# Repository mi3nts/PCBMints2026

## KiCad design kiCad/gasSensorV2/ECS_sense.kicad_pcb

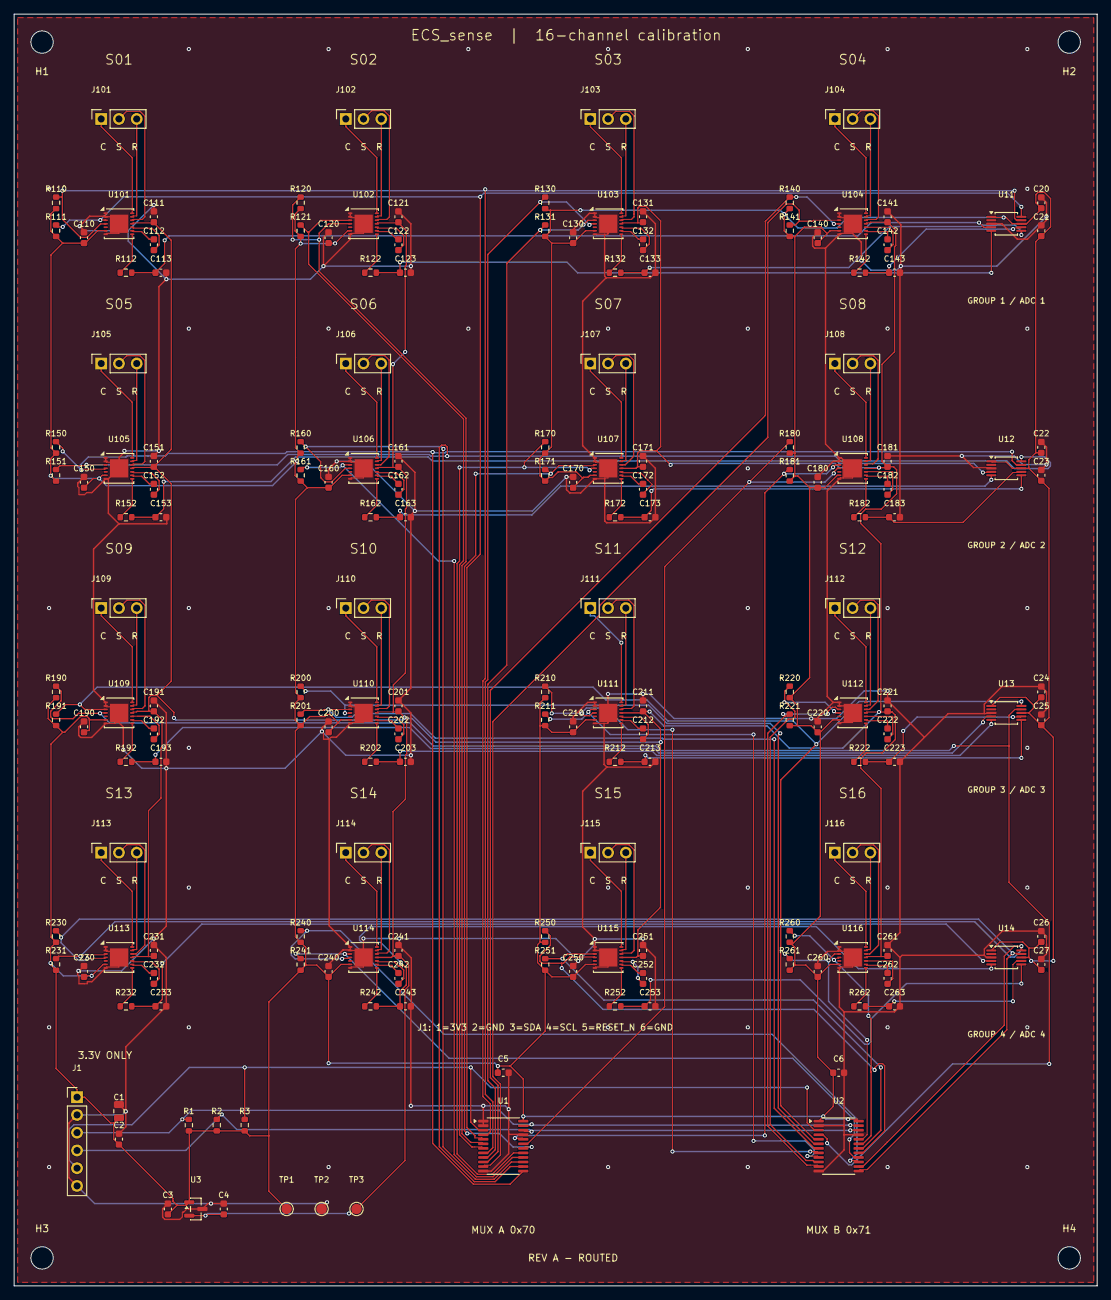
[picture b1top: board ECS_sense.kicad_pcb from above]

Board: 2 copper layers, 155.0 x 182.0 mm, 176 parts (0 on the bottom side), 150 nets.

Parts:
C1: 10uF / 10V; C_0805_2012Metric
C2, C5, C6, C20, C22, C24, C26, C110, C111, C113, C120, C121, C123, C130, C131, C133, C140, C141, C143, C150, C151, C153, C160, C161, C163, C170, C171, C173, C180, C181, C183, C190, C191, C193, C200, C201, C203, C210, C211, C213, C220, C221, C223, C230, C231, C233, C240, C241, C243, C250, C251, C253, C260, C261, C263: 100nF; C_0603_1608Metric
C3, C4, C21, C23, C25, C27: 1uF; C_0603_1608Metric
C112, C122, C132, C142, C152, C162, C172, C182, C192, C202, C212, C222, C232, C242, C252, C262: 10nF C0G; C_0603_1608Metric
H1, H2, H3, H4: MountingHole_3.2mm_M3
J1: MCU: 3V3 / GND / SDA / SCL / RESET / GND; PinHeader_1x06_P2.54mm_Vertical
J101, J102, J103, J104, J105, J106, J107, J108, J109, J110, J111, J112, J113, J114, J115, J116: ES1 port: C / S / R; PinSocket_1x03_P2.54mm_Vertical
R1, R2: 4.7k; R_0603_1608Metric
R3, R110, R111, R120, R121, R130, R131, R140, R141, R150, R151, R160, R161, R170, R171, R180, R181, R190, R191, R200, R201, R210, R211, R220, R221, R230, R231, R240, R241, R250, R251, R260, R261: 10k; R_0603_1608Metric
R112, R122, R132, R142, R152, R162, R172, R182, R192, R202, R212, R222, R232, R242, R252, R262: 100R; R_0603_1608Metric
TP1: 3V3; TestPoint_Pad_D1.5mm
TP2: GND; TestPoint_Pad_D1.5mm
TP3: 2V5; TestPoint_Pad_D1.5mm
U1, U2: TCA9548APWR; TSSOP-24_4.4x7.8mm_P0.65mm
U3: REF3025AIDBZR; SOT-23
U11, U12, U13, U14: ADS1115IDGS; TSSOP-10_3x3mm_P0.5mm
U101, U102, U103, U104, U105, U106, U107, U108, U109, U110, U111, U112, U113, U114, U115, U116: LMP91000SD; WSON-14-1EP_4.0x4.0mm_P0.5mm_EP2.6x2.6mm

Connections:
+3V3: C1.1, C2.1, C3.1, C5.1, C6.1, C20.1, C21.1, C22.1, C23.1, C24.1, C25.1, C26.1, C27.1, C110.1, C120.1, C130.1, C140.1, C150.1, C160.1, C170.1, C180.1, C190.1, C200.1, C210.1, C220.1, C230.1, C240.1, C250.1, C260.1, J1.1, R1.1, R2.1, R3.1, R110.1, R111.1, R120.1, R121.1, R130.1, R131.1, R140.1, R141.1, R150.1, R151.1, R160.1, R161.1, R170.1, R171.1, R180.1, R181.1, R190.1, R191.1, R200.1, R201.1, R210.1, R211.1, R220.1, R221.1, R230.1, R231.1, R240.1, R241.1, R250.1, R251.1, R260.1, R261.1, TP1.1 (1_1), U1.24 (VCC), U2.1 (A0), U2.24 (VCC), U3.1 (IN), U11.1 (ADDR), U11.8 (VDD), U12.1 (ADDR), U12.8 (VDD), U13.1 (ADDR), U13.8 (VDD), U14.1 (ADDR), U14.8 (VDD), U101.6 (VDD), U102.6 (VDD), U103.6 (VDD), U104.6 (VDD), U105.6 (VDD), U106.6 (VDD), U107.6 (VDD), U108.6 (VDD), U109.6 (VDD), U110.6 (VDD), U111.6 (VDD), U112.6 (VDD), U113.6 (VDD), U114.6 (VDD), U115.6 (VDD), U116.6 (VDD)
GND: C1.2, C2.2, C3.2, C4.2, C5.2, C6.2, C20.2, C21.2, C22.2, C23.2, C24.2, C25.2, C26.2, C27.2, C110.2, C111.2, C113.2, C120.2, C121.2, C123.2, C130.2, C131.2, C133.2, C140.2, C141.2, C143.2, C150.2, C151.2, C153.2, C160.2, C161.2, C163.2, C170.2, C171.2, C173.2, C180.2, C181.2, C183.2, C190.2, C191.2, C193.2, C200.2, C201.2, C203.2, C210.2, C211.2, C213.2, C220.2, C221.2, C223.2, C230.2, C231.2, C233.2, C240.2, C241.2, C243.2, C250.2, C251.2, C253.2, C260.2, C261.2, C263.2, J1.2, J1.6, TP2.1 (1_1), U1.1 (A0), U1.2 (A1), U1.12 (GND), U1.21 (A2), U2.2 (A1), U2.12 (GND), U2.21 (A2), U3.3 (GND), U11.3 (GND), U12.3 (GND), U13.3 (GND), U14.3 (GND), U101.1 (DGND), U101.2 (~MENB), U101.7 (AGND), U101.15 (DAP), U102.1 (DGND), U102.2 (~MENB), U102.7 (AGND), U102.15 (DAP), U103.1 (DGND), U103.2 (~MENB), U103.7 (AGND), U103.15 (DAP), U104.1 (DGND), U104.2 (~MENB), U104.7 (AGND), U104.15 (DAP), U105.1 (DGND), U105.2 (~MENB), U105.7 (AGND), U105.15 (DAP), U106.1 (DGND), U106.2 (~MENB), U106.7 (AGND), U106.15 (DAP), U107.1 (DGND), U107.2 (~MENB), U107.7 (AGND), U107.15 (DAP), U108.1 (DGND), U108.2 (~MENB), U108.7 (AGND), U108.15 (DAP), U109.1 (DGND), U109.2 (~MENB), U109.7 (AGND), U109.15 (DAP), U110.1 (DGND), U110.2 (~MENB), U110.7 (AGND), U110.15 (DAP), U111.1 (DGND), U111.2 (~MENB), U111.7 (AGND), U111.15 (DAP), U112.1 (DGND), U112.2 (~MENB), U112.7 (AGND), U112.15 (DAP), U113.1 (DGND), U113.2 (~MENB), U113.7 (AGND), U113.15 (DAP), U114.1 (DGND), U114.2 (~MENB), U114.7 (AGND), U114.15 (DAP), U115.1 (DGND), U115.2 (~MENB), U115.7 (AGND), U115.15 (DAP), U116.1 (DGND), U116.2 (~MENB), U116.7 (AGND), U116.15 (DAP)
MUX_RESET_N: J1.5, R3.2, U1.3 (~RESET), U2.3 (~RESET)
S01_ADC: C113.1, R112.2, U11.4 (AIN0)
S01_C1: C112.1, U101.10 (C1)
S01_C2: C112.2, U101.9 (C2)
S01_CE: J101.1, U101.14 (CE)
S01_RE: J101.3, U101.13 (RE)
S01_SCL: R111.2, U1.5 (SC0), U11.10 (SCL), U101.3 (SCL)
S01_SDA: R110.2, U1.4 (SD0), U11.9 (SDA), U101.4 (SDA)
S01_VOUT: R112.1, U101.8 (VOUT)
S01_WE: J101.2, U101.12 (WE)
S02_ADC: C123.1, R122.2, U11.5 (AIN1)
S02_C1: C122.1, U102.10 (C1)
S02_C2: C122.2, U102.9 (C2)
S02_CE: J102.1, U102.14 (CE)
S02_RE: J102.3, U102.13 (RE)
S02_SCL: R121.2, U1.7 (SC1), U102.3 (SCL)
S02_SDA: R120.2, U1.6 (SD1), U102.4 (SDA)
S02_VOUT: R122.1, U102.8 (VOUT)
S02_WE: J102.2, U102.12 (WE)
S03_ADC: C133.1, R132.2, U11.6 (AIN2)
S03_C1: C132.1, U103.10 (C1)
S03_C2: C132.2, U103.9 (C2)
S03_CE: J103.1, U103.14 (CE)
S03_RE: J103.3, U103.13 (RE)
S03_SCL: R131.2, U1.9 (SC2), U103.3 (SCL)
S03_SDA: R130.2, U1.8 (SD2), U103.4 (SDA)
S03_VOUT: R132.1, U103.8 (VOUT)
S03_WE: J103.2, U103.12 (WE)
S04_ADC: C143.1, R142.2, U11.7 (AIN3)
S04_C1: C142.1, U104.10 (C1)
S04_C2: C142.2, U104.9 (C2)
S04_CE: J104.1, U104.14 (CE)
S04_RE: J104.3, U104.13 (RE)
S04_SCL: R141.2, U1.11 (SC3), U104.3 (SCL)
S04_SDA: R140.2, U1.10 (SD3), U104.4 (SDA)
S04_VOUT: R142.1, U104.8 (VOUT)
S04_WE: J104.2, U104.12 (WE)
S05_ADC: C153.1, R152.2, U12.4 (AIN0)
S05_C1: C152.1, U105.10 (C1)
S05_C2: C152.2, U105.9 (C2)
S05_CE: J105.1, U105.14 (CE)
S05_RE: J105.3, U105.13 (RE)
S05_SCL: R151.2, U1.14 (SC4), U12.10 (SCL), U105.3 (SCL)
S05_SDA: R150.2, U1.13 (SD4), U12.9 (SDA), U105.4 (SDA)
S05_VOUT: R152.1, U105.8 (VOUT)
S05_WE: J105.2, U105.12 (WE)
S06_ADC: C163.1, R162.2, U12.5 (AIN1)
S06_C1: C162.1, U106.10 (C1)
S06_C2: C162.2, U106.9 (C2)
S06_CE: J106.1, U106.14 (CE)
S06_RE: J106.3, U106.13 (RE)
S06_SCL: R161.2, U1.16 (SC5), U106.3 (SCL)
S06_SDA: R160.2, U1.15 (SD5), U106.4 (SDA)
S06_VOUT: R162.1, U106.8 (VOUT)
S06_WE: J106.2, U106.12 (WE)
S07_ADC: C173.1, R172.2, U12.6 (AIN2)
S07_C1: C172.1, U107.10 (C1)
S07_C2: C172.2, U107.9 (C2)
S07_CE: J107.1, U107.14 (CE)
S07_RE: J107.3, U107.13 (RE)
S07_SCL: R171.2, U1.18 (SC6), U107.3 (SCL)
S07_SDA: R170.2, U1.17 (SD6), U107.4 (SDA)
S07_VOUT: R172.1, U107.8 (VOUT)
S07_WE: J107.2, U107.12 (WE)
S08_ADC: C183.1, R182.2, U12.7 (AIN3)
S08_C1: C182.1, U108.10 (C1)
S08_C2: C182.2, U108.9 (C2)
S08_CE: J108.1, U108.14 (CE)
S08_RE: J108.3, U108.13 (RE)
S08_SCL: R181.2, U1.20 (SC7), U108.3 (SCL)
S08_SDA: R180.2, U1.19 (SD7), U108.4 (SDA)
S08_VOUT: R182.1, U108.8 (VOUT)
S08_WE: J108.2, U108.12 (WE)
S09_ADC: C193.1, R192.2, U13.4 (AIN0)
S09_C1: C192.1, U109.10 (C1)
S09_C2: C192.2, U109.9 (C2)
S09_CE: J109.1, U109.14 (CE)
S09_RE: J109.3, U109.13 (RE)
S09_SCL: R191.2, U2.5 (SC0), U13.10 (SCL), U109.3 (SCL)
S09_SDA: R190.2, U2.4 (SD0), U13.9 (SDA), U109.4 (SDA)
S09_VOUT: R192.1, U109.8 (VOUT)
S09_WE: J109.2, U109.12 (WE)
S10_ADC: C203.1, R202.2, U13.5 (AIN1)
S10_C1: C202.1, U110.10 (C1)
S10_C2: C202.2, U110.9 (C2)
S10_CE: J110.1, U110.14 (CE)
S10_RE: J110.3, U110.13 (RE)
S10_SCL: R201.2, U2.7 (SC1), U110.3 (SCL)
S10_SDA: R200.2, U2.6 (SD1), U110.4 (SDA)
S10_VOUT: R202.1, U110.8 (VOUT)
S10_WE: J110.2, U110.12 (WE)
S11_ADC: C213.1, R212.2, U13.6 (AIN2)
S11_C1: C212.1, U111.10 (C1)
S11_C2: C212.2, U111.9 (C2)
S11_CE: J111.1, U111.14 (CE)
S11_RE: J111.3, U111.13 (RE)
S11_SCL: R211.2, U2.9 (SC2), U111.3 (SCL)
S11_SDA: R210.2, U2.8 (SD2), U111.4 (SDA)
S11_VOUT: R212.1, U111.8 (VOUT)
S11_WE: J111.2, U111.12 (WE)
S12_ADC: C223.1, R222.2, U13.7 (AIN3)
S12_C1: C222.1, U112.10 (C1)
S12_C2: C222.2, U112.9 (C2)
S12_CE: J112.1, U112.14 (CE)
S12_RE: J112.3, U112.13 (RE)
S12_SCL: R221.2, U2.11 (SC3), U112.3 (SCL)
S12_SDA: R220.2, U2.10 (SD3), U112.4 (SDA)
S12_VOUT: R222.1, U112.8 (VOUT)
S12_WE: J112.2, U112.12 (WE)
S13_ADC: C233.1, R232.2, U14.4 (AIN0)
S13_C1: C232.1, U113.10 (C1)
S13_C2: C232.2, U113.9 (C2)
S13_CE: J113.1, U113.14 (CE)
S13_RE: J113.3, U113.13 (RE)
S13_SCL: R231.2, U2.14 (SC4), U14.10 (SCL), U113.3 (SCL)
S13_SDA: R230.2, U2.13 (SD4), U14.9 (SDA), U113.4 (SDA)
S13_VOUT: R232.1, U113.8 (VOUT)
S13_WE: J113.2, U113.12 (WE)
S14_ADC: C243.1, R242.2, U14.5 (AIN1)
S14_C1: C242.1, U114.10 (C1)
S14_C2: C242.2, U114.9 (C2)
S14_CE: J114.1, U114.14 (CE)
S14_RE: J114.3, U114.13 (RE)
S14_SCL: R241.2, U2.16 (SC5), U114.3 (SCL)
S14_SDA: R240.2, U2.15 (SD5), U114.4 (SDA)
S14_VOUT: R242.1, U114.8 (VOUT)
S14_WE: J114.2, U114.12 (WE)
S15_ADC: C253.1, R252.2, U14.6 (AIN2)
S15_C1: C252.1, U115.10 (C1)
S15_C2: C252.2, U115.9 (C2)
S15_CE: J115.1, U115.14 (CE)
S15_RE: J115.3, U115.13 (RE)
S15_SCL: R251.2, U2.18 (SC6), U115.3 (SCL)
S15_SDA: R250.2, U2.17 (SD6), U115.4 (SDA)
S15_VOUT: R252.1, U115.8 (VOUT)
S15_WE: J115.2, U115.12 (WE)
S16_ADC: C263.1, R262.2, U14.7 (AIN3)
S16_C1: C262.1, U116.10 (C1)
S16_C2: C262.2, U116.9 (C2)
S16_CE: J116.1, U116.14 (CE)
S16_RE: J116.3, U116.13 (RE)
S16_SCL: R261.2, U2.20 (SC7), U116.3 (SCL)
S16_SDA: R260.2, U2.19 (SD7), U116.4 (SDA)
S16_VOUT: R262.1, U116.8 (VOUT)
S16_WE: J116.2, U116.12 (WE)
SCL: J1.4, R2.2, U1.22 (SCL), U2.22 (SCL)
SDA: J1.3, R1.2, U1.23 (SDA), U2.23 (SDA)
VREF_2V5: C4.1, C111.1, C121.1, C131.1, C141.1, C151.1, C161.1, C171.1, C181.1, C191.1, C201.1, C211.1, C221.1, C231.1, C241.1, C251.1, C261.1, TP3.1 (1_1), U3.2 (OUT), U101.11 (VREF), U102.11 (VREF), U103.11 (VREF), U104.11 (VREF), U105.11 (VREF), U106.11 (VREF), U107.11 (VREF), U108.11 (VREF), U109.11 (VREF), U110.11 (VREF), U111.11 (VREF), U112.11 (VREF), U113.11 (VREF), U114.11 (VREF), U115.11 (VREF), U116.11 (VREF)

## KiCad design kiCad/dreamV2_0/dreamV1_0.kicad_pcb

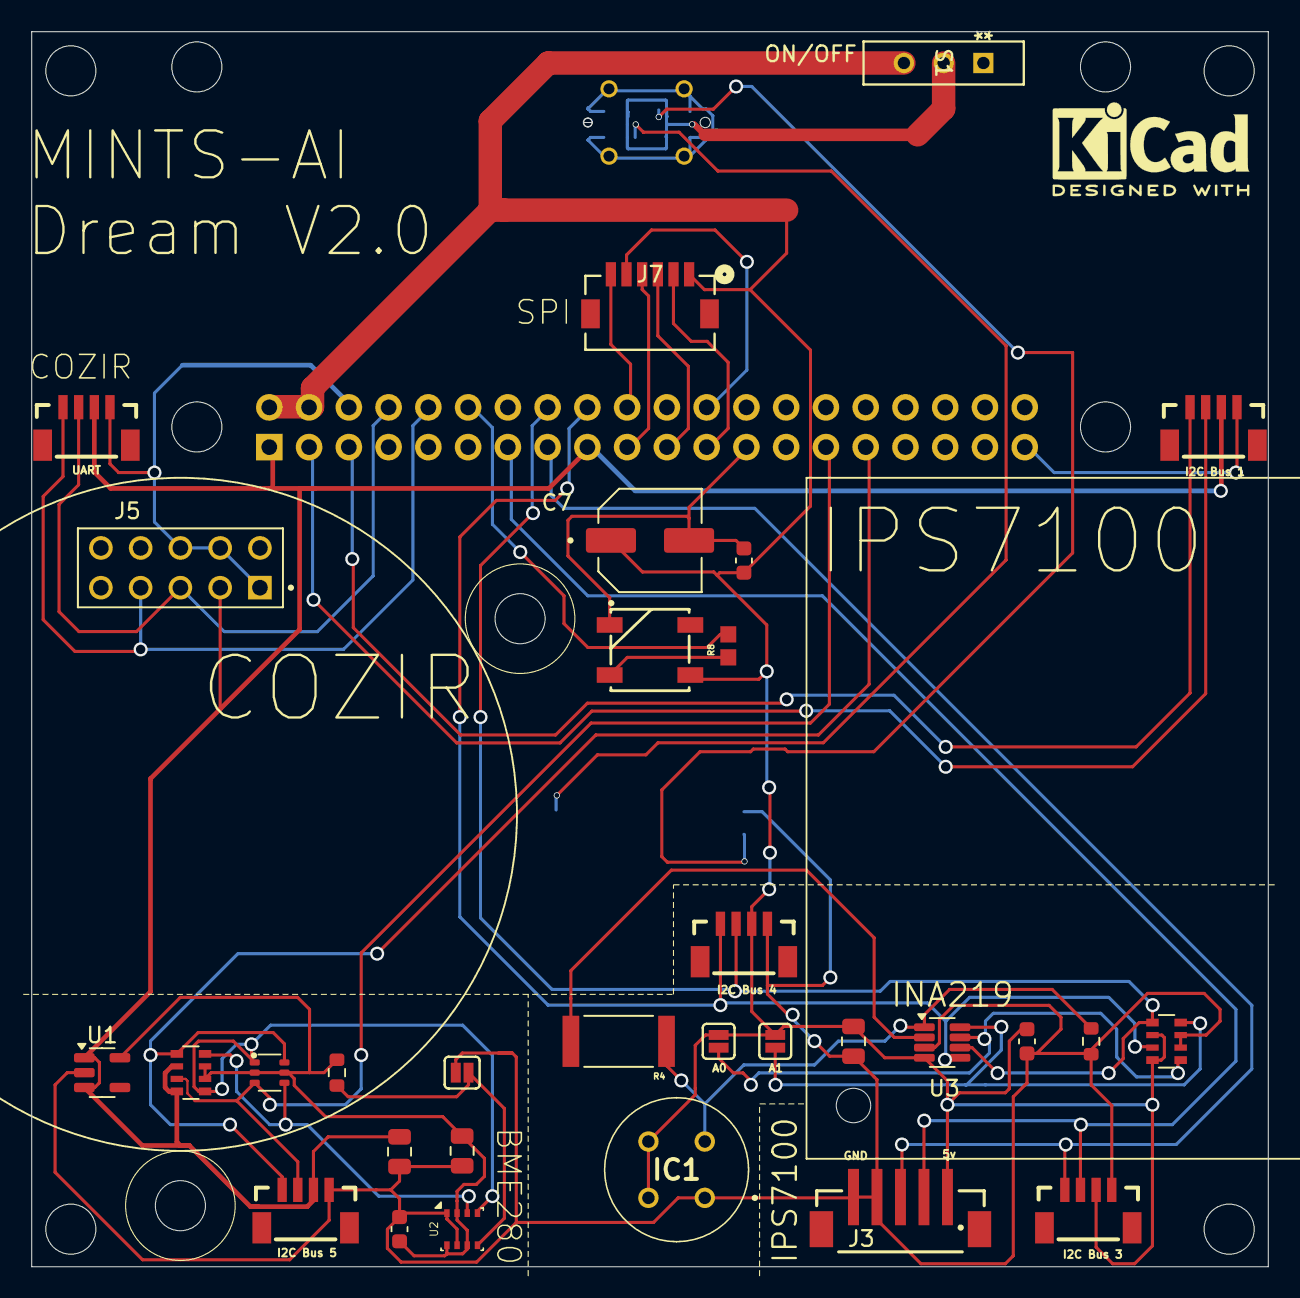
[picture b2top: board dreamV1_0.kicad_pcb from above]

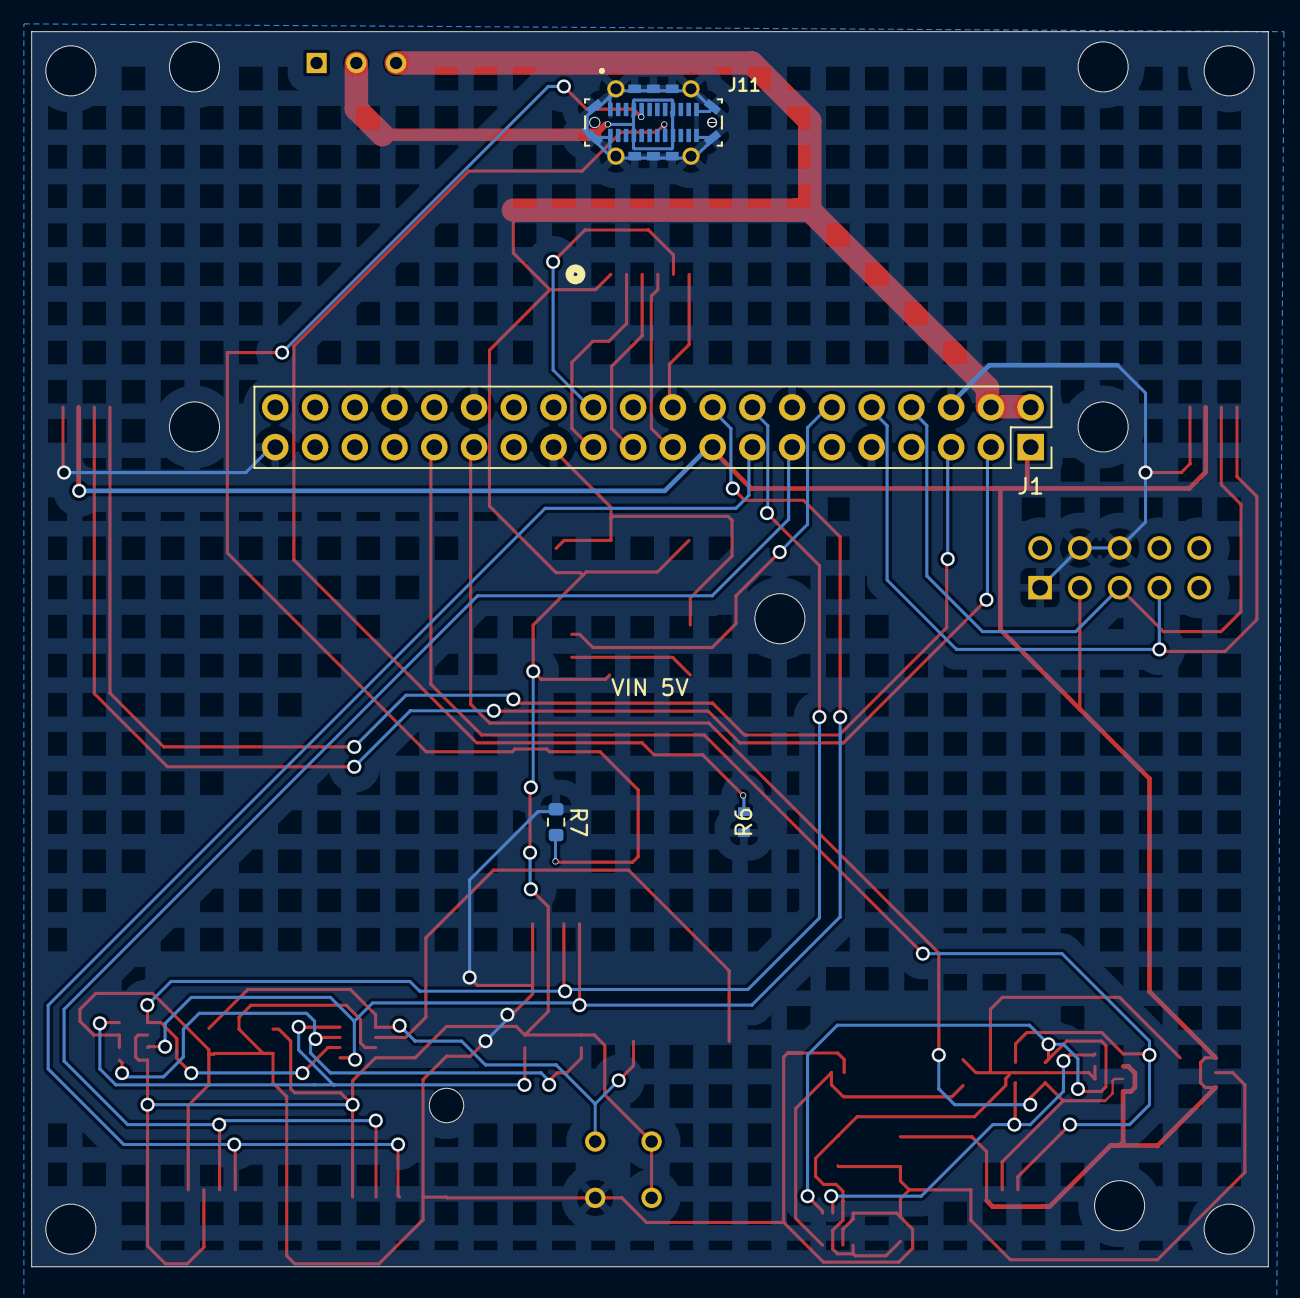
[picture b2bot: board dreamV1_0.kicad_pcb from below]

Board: 2 copper layers, 79.0 x 78.9 mm, 35 parts (4 on the bottom side), 30 nets.

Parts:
C1, C5, C6: 0.1uF; C_0603_1608Metric
C2, C3, C4: 10uF; C_0805_2012Metric
C7: EEV107M010S9GAA
D1: WS2812B_5050; WS2812_5050-4Pin
IC1: TGS2611-C00; TGS2611C00
J1: GPIO; PinSocket_2x20_P2.54mm_Vertical
J2, J4, J6, J8, J9: Qwiic_Vertical; JST_SMD_1.0mm-4_Vertical_Black
J3: 679305124022
J5: M20-7830542
J7: 5013310607
J11: 10132328-10011LF
JP1, JP2, JP3: Jumper_2_NO
Q1: BSS138; SOT-363
R1, R5: 10k; R_Array_Convex_4x0603
R2, R3: 10k; R_0603_1608Metric
R4: PT2512FK-070R1L
R6: RC0603FR-075K1L; RC0603N_YAG-L
R7: RC0603FR-075K1L; R_0603_1608Metric
R8: RC0603FR-07330RL
S1: NK236; SWITCH_NK236_APM
U1: AP2112K-3.3; SOT-23-5
U2: BME280; Bosch_LGA-8_2.5x2.5mm_P0.65mm_ClockwisePinNumbering
U3: INA219BxDCN; SOT-23-8

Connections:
+3V3: C2.1, J1.1, J1.17, J2.2, J5.3, J6.2, J9.2, R1.2, R1.4, U1.1 (VIN), U1.3 (EN)
+5V: C4.1, C5.1, C6.1, C7.P, D1.1 (VDD), IC1.3 (SENSOR_ELECTRODE_(+)), IC1.4 (HEATER_2), J1.2, J1.4, J3.1, J4.2, J7.1, J8.2, JP2.2 (B), JP3.2 (B), R5.2, R5.4, S1.2 (A), U3.4 (VS)
/5V_BUS_USB: J11.A4 (VBUS_A4), J11.A9 (VBUS_A9), J11.B4 (VBUS_B4), J11.B9 (VBUS_B9), S1.1 (com)
/BME_ADD: JP1.2 (B), R2.1, U2.5 (SDO)
/BME_SCL: Q1.1 (S), R1.5, U2.4 (SCK)
/BME_SDA: Q1.4 (S), R1.8, U2.3 (SDI)
/GPIO2/SDA1: J1.3, J9.3
/GPIO3/SCL1: J1.5, J9.4
/GPIO5/SDA5: J1.29, J2.3, Q1.3 (D), R1.3
/GPIO6/SCL5: J1.31, J2.4, Q1.6 (D), R1.1
/GPIO8/SPI0.CE0: J1.24, J7.5
/GPIO9/SPI0.MISO: J1.21, J7.3
/GPIO10/SPI0.MOSI: J1.19, J7.4
/GPIO11/SPI0.SCLK: J1.23, J7.2
/GPIO14/TXD0: J1.8, J5.5, J6.3
/GPIO15/RXD0: J1.10, J5.7, J6.4
/GPIO18/PCM.CLK: J1.12, R8.2
/GPIO22/SCL3: J1.15, J3.3, J4.4
/GPIO23/SDA4: J1.16, J8.3, R5.1, U3.6 (SDA)
/GPIO24/SCL4: J1.18, J8.4, R5.3, U3.5 (SCL)
/GPIO27/SDA3: J1.13, J3.2, J4.3
/INA+: IC1.2 (SENSOR_ELECTRODE_(-)), R3.2, R4.1, U3.1 (IN+)
/INA_ADD0: JP2.1 (A), R5.5, U3.7 (A0)
/INA_ADD1: JP3.1 (A), R5.8, U3.8 (A1)
BME_3V3: C1.1, C3.1, Q1.2 (G), Q1.5 (G), R1.6, R1.7, R2.2, U1.5 (VOUT), U2.2 (CSB), U2.6 (VDDIO), U2.8 (VDD)
GND: C1.2, C2.2, C3.2, C4.2, C5.2, C6.2, C7.N, D1.3 (VSS), IC1.1 (HEATER_1), J1.6, J1.9, J1.14, J1.20, J1.25, J1.30, J1.34, J1.39, J2.1, J3.4, J3.5, J4.1, J5.1, J5.4, J5.6, J6.1, J7.6, J8.1, J9.1, J11.1 (SHIELD), J11.2 (SHIELD__1), J11.3 (SHIELD__2), J11.4 (SHIELD__3), J11.5 (SHIELD__4), J11.6 (SHIELD__5), J11.7 (SHIELD__6), J11.8 (SHIELD__7), J11.9 (SHIELD__8), J11.10 (SHIELD__9), J11.11 (SHIELD__10), J11.12 (SHIELD__11), J11.13 (SHIELD__12), J11.14 (SHIELD__13), J11.A1 (GND_A1), J11.A12 (GND_A12), J11.B1 (GND_B1), J11.B12 (GND_B12), JP1.1 (A), R3.1, R5.6, R5.7, R6.1, R7.1, U1.2 (GND), U2.1 (GND), U2.7 (GND), U3.3 (GND)
unnamed: D1.4 (DIN), R8.1
unnamed: J11.A5 (CC1), R7.2
unnamed: J11.B5 (CC2), R6.2
unnamed: R4.2, U3.2 (IN-)

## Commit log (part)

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2026-01-16 NEW PCBMINTS 2026 + dream2.0 fixes
